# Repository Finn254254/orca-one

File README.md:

<div align="center">

# Orca One V1.0

### A custom Allwinner V3s single-board computer

Hardware design · PCB layout · ORCA OS testing · Bring-up documentation

</div>

> [!IMPORTANT]
> **Open-source hardware.** Orca One V1.0 is released under the CERN Open Hardware Licence Version 2 - Strongly Reciprocal (CERN-OHL-S-2.0). You may study, modify, manufacture, and redistribute the design subject to the license terms. See [LICENSE](LICENSE).

> [!WARNING]
> **Early hardware revision.** Orca One V1.0 has not been manufactured or tested yet. The board is currently waiting on funding before manufacturing.

## What is Orca One?

Orca One is the first test board for Orca servers. The main purpose of the board is to give us our own hardware to start testing ORCA OS on.

The first goal is simple: get our lightweight Linux-based ORCA OS to successfully boot on hardware we designed ourselves. This board is not meant to be a powerful Orca server yet. It is a starting point for testing the hardware and software before moving onto more complicated boards.

## Board renders

| Front | Back |
| :---: | :---: |
|  |  |

## Why I chose the Allwinner V3s

I chose the Allwinner V3s because it is a relatively easy and cheap chip to start with.

One of the biggest reasons was its package. The V3s uses an LQFP package instead of BGA, which makes the PCB easier to design and also makes the chip easier to solder.

It also has integrated RAM instead of requiring external DDR. This means I don't have to route a separate DDR chip for my first Linux board, while I can still get experience designing a board around a Linux-capable SoC.

## Main features

- Allwinner V3s SoC with integrated RAM
- 5 V USB-C power input
- 3.3 V, 3.0 V, 1.8 V, 1.2 V and 1.1 V power rails
- MicroSD storage and OS boot
- USB-A 2.0
- Ethernet
- GPIO expansion
- UART debugging
- Fan header
- Four-layer custom PCB

## Power system

The board is powered using 5 V over USB-C. The USB-C input is configured as a power sink using two 5.1 kΩ resistors on the CC pins.

From the 5 V input, the board generates the different voltages required by the V3s and the other parts of the board. These include 3.3 V, 3.0 V, 1.8 V, 1.2 V and 1.1 V.

I decided to design this power system instead of using a premade power module because I wanted to learn and get practice using power regulators and buck converters.

One of the main things I had to learn was how adjustable regulators use a feedback voltage divider. I had to use the regulator equations to work out the resistor values needed to generate the correct output voltages.

This was probably the hardest part of designing the schematic because it involved both understanding the circuit and doing the maths to make sure each rail had the correct voltage.

## Decoupling and bulk capacitors

Another part of the power design was adding the decoupling and bulk capacitors for the different rails.

This became one of the hardest parts when I moved onto the PCB layout. I needed to fit the capacitors close to the V3s power pins while still leaving enough room around the SoC to route everything else.

## MicroSD and ORCA OS

Orca One does not have any other onboard storage, so the MicroSD card is used to store and boot ORCA OS.

The first major software test for the physical board will be seeing if our OS can successfully boot from the MicroSD card.

## USB 2.0

Orca One has a USB-A 2.0 port for connecting USB devices to the board.

## Ethernet

Ethernet was added so Orca One can be managed remotely over the network using SSH.

This means that once ORCA OS is running, I should be able to connect to the board from another computer and manage it without needing a display or keyboard connected directly to Orca One.

## GPIO, UART and fan

The board also has headers for GPIO, UART and a fan.

UART gives me a way to debug the board, especially during the first boot attempts. The GPIO header exposes connections from the V3s for future testing and expansion, while the fan header gives the board a connection for cooling if needed.

## PCB layout

After completing the schematic, I moved onto designing the four-layer PCB.

One of the most difficult parts was placing the decoupling and bulk capacitors close to the SoC while also making sure there was enough room to route the rest of the board.

I also spent a lot of time working on the copper pours. The pours were changed many times during the PCB design as I worked out better ways to shape and position them around the board.

This ended up being one of the biggest things I learned from designing Orca One. Before this project I had much less experience using copper pours, but I now have a much better understanding of how to use and adjust them as part of a PCB layout.

## What I learned

Orca One has given me practice designing a complete board around a Linux-capable SoC instead of only working with individual smaller circuits.

Some of the main things I learned while making the board were:

- How to use and shape copper pours
- How to design multiple power rails
- How adjustable regulators and buck converters work
- How to calculate feedback voltage dividers
- How to place decoupling and bulk capacitors around an SoC
- How to design a board around a processor with multiple interfaces
- How the hardware and boot storage need to work together to boot an operating system

The biggest thing I learned during the PCB layout was how to use copper pours properly. I changed them several times while designing the board and gradually found better ways to fit them into the layout.

## Current status

Orca One V1.0 is currently waiting on funding before it can be manufactured.

Because the physical board does not exist yet, none of the hardware has been validated. The next major stage of the project is manufacturing and bring-up.

## First bring-up

Once the board has been manufactured and assembled, the first thing I want to find out is whether it powers on correctly.

After that, the main goal is to see if it can successfully boot ORCA OS from the MicroSD card.

Getting the board to power on and boot our own OS will be the first major test of Orca One and will let us start testing the hardware and software together.

## Design overview

The complete editable schematic is included in the KiCad project. Expand a section below for a quick visual tour.

<details>
<summary><strong>Power system</strong> — USB-C input and regulated power rails</summary>

### USB-C power input

### Regulated power rails

</details>

<details>
<summary><strong>External interfaces</strong> — USB-A, MicroSD, and Ethernet</summary>

### USB-A 2.0

### MicroSD card

### Ethernet

</details>

<details>
<summary><strong>Processor and supporting circuitry</strong> — Allwinner V3s and decoupling</summary>

### Decoupling and bulk capacitors

</details>

<details>
<summary><strong>Expansion and debug</strong> — fan, UART, and GPIO headers</summary>

</details>

## Repository contents

| Path | Contents |
| --- | --- |
| `hardware/kicad/` | KiCad 9 project, schematic, and four-layer PCB layout |
| `hardware/footprints/` | Custom Allwinner V3s LQFP-128 footprint |
| `bom/` | Bill of materials in CSV and XLSX formats |
| `manufacturing/` | Gerber/drill archive and component placement data |
| `images/` | Board photographs, schematic images and renders |

## Opening the design

1. Install KiCad 9 or a compatible newer release.
2. Open `hardware/kicad/ORCA First Linux Board.kicad_pro`.
3. The project-local footprint table maps the included `v3s` footprint library automatically.

The PCB currently references three optional component STEP models from the original designer's local computer, including the V3s processor and Ethernet connector models. They are not included, so KiCad may show those packages without 3D bodies until redistributable models are added.

## Manufacturing warning

Review the schematic, PCB, BOM, placement data, and fabrication outputs carefully before ordering or assembling boards.

This is the first hardware revision and has not yet been physically tested. Manufacturing outputs may also become stale as the editable design changes.

## License

Copyright © 2026 Finn Mather.

Orca One V1.0 is open-source hardware licensed under **CERN-OHL-S-2.0**. You may study, modify, manufacture, and redistribute the design under the terms of the license. See [LICENSE](LICENSE) for details.

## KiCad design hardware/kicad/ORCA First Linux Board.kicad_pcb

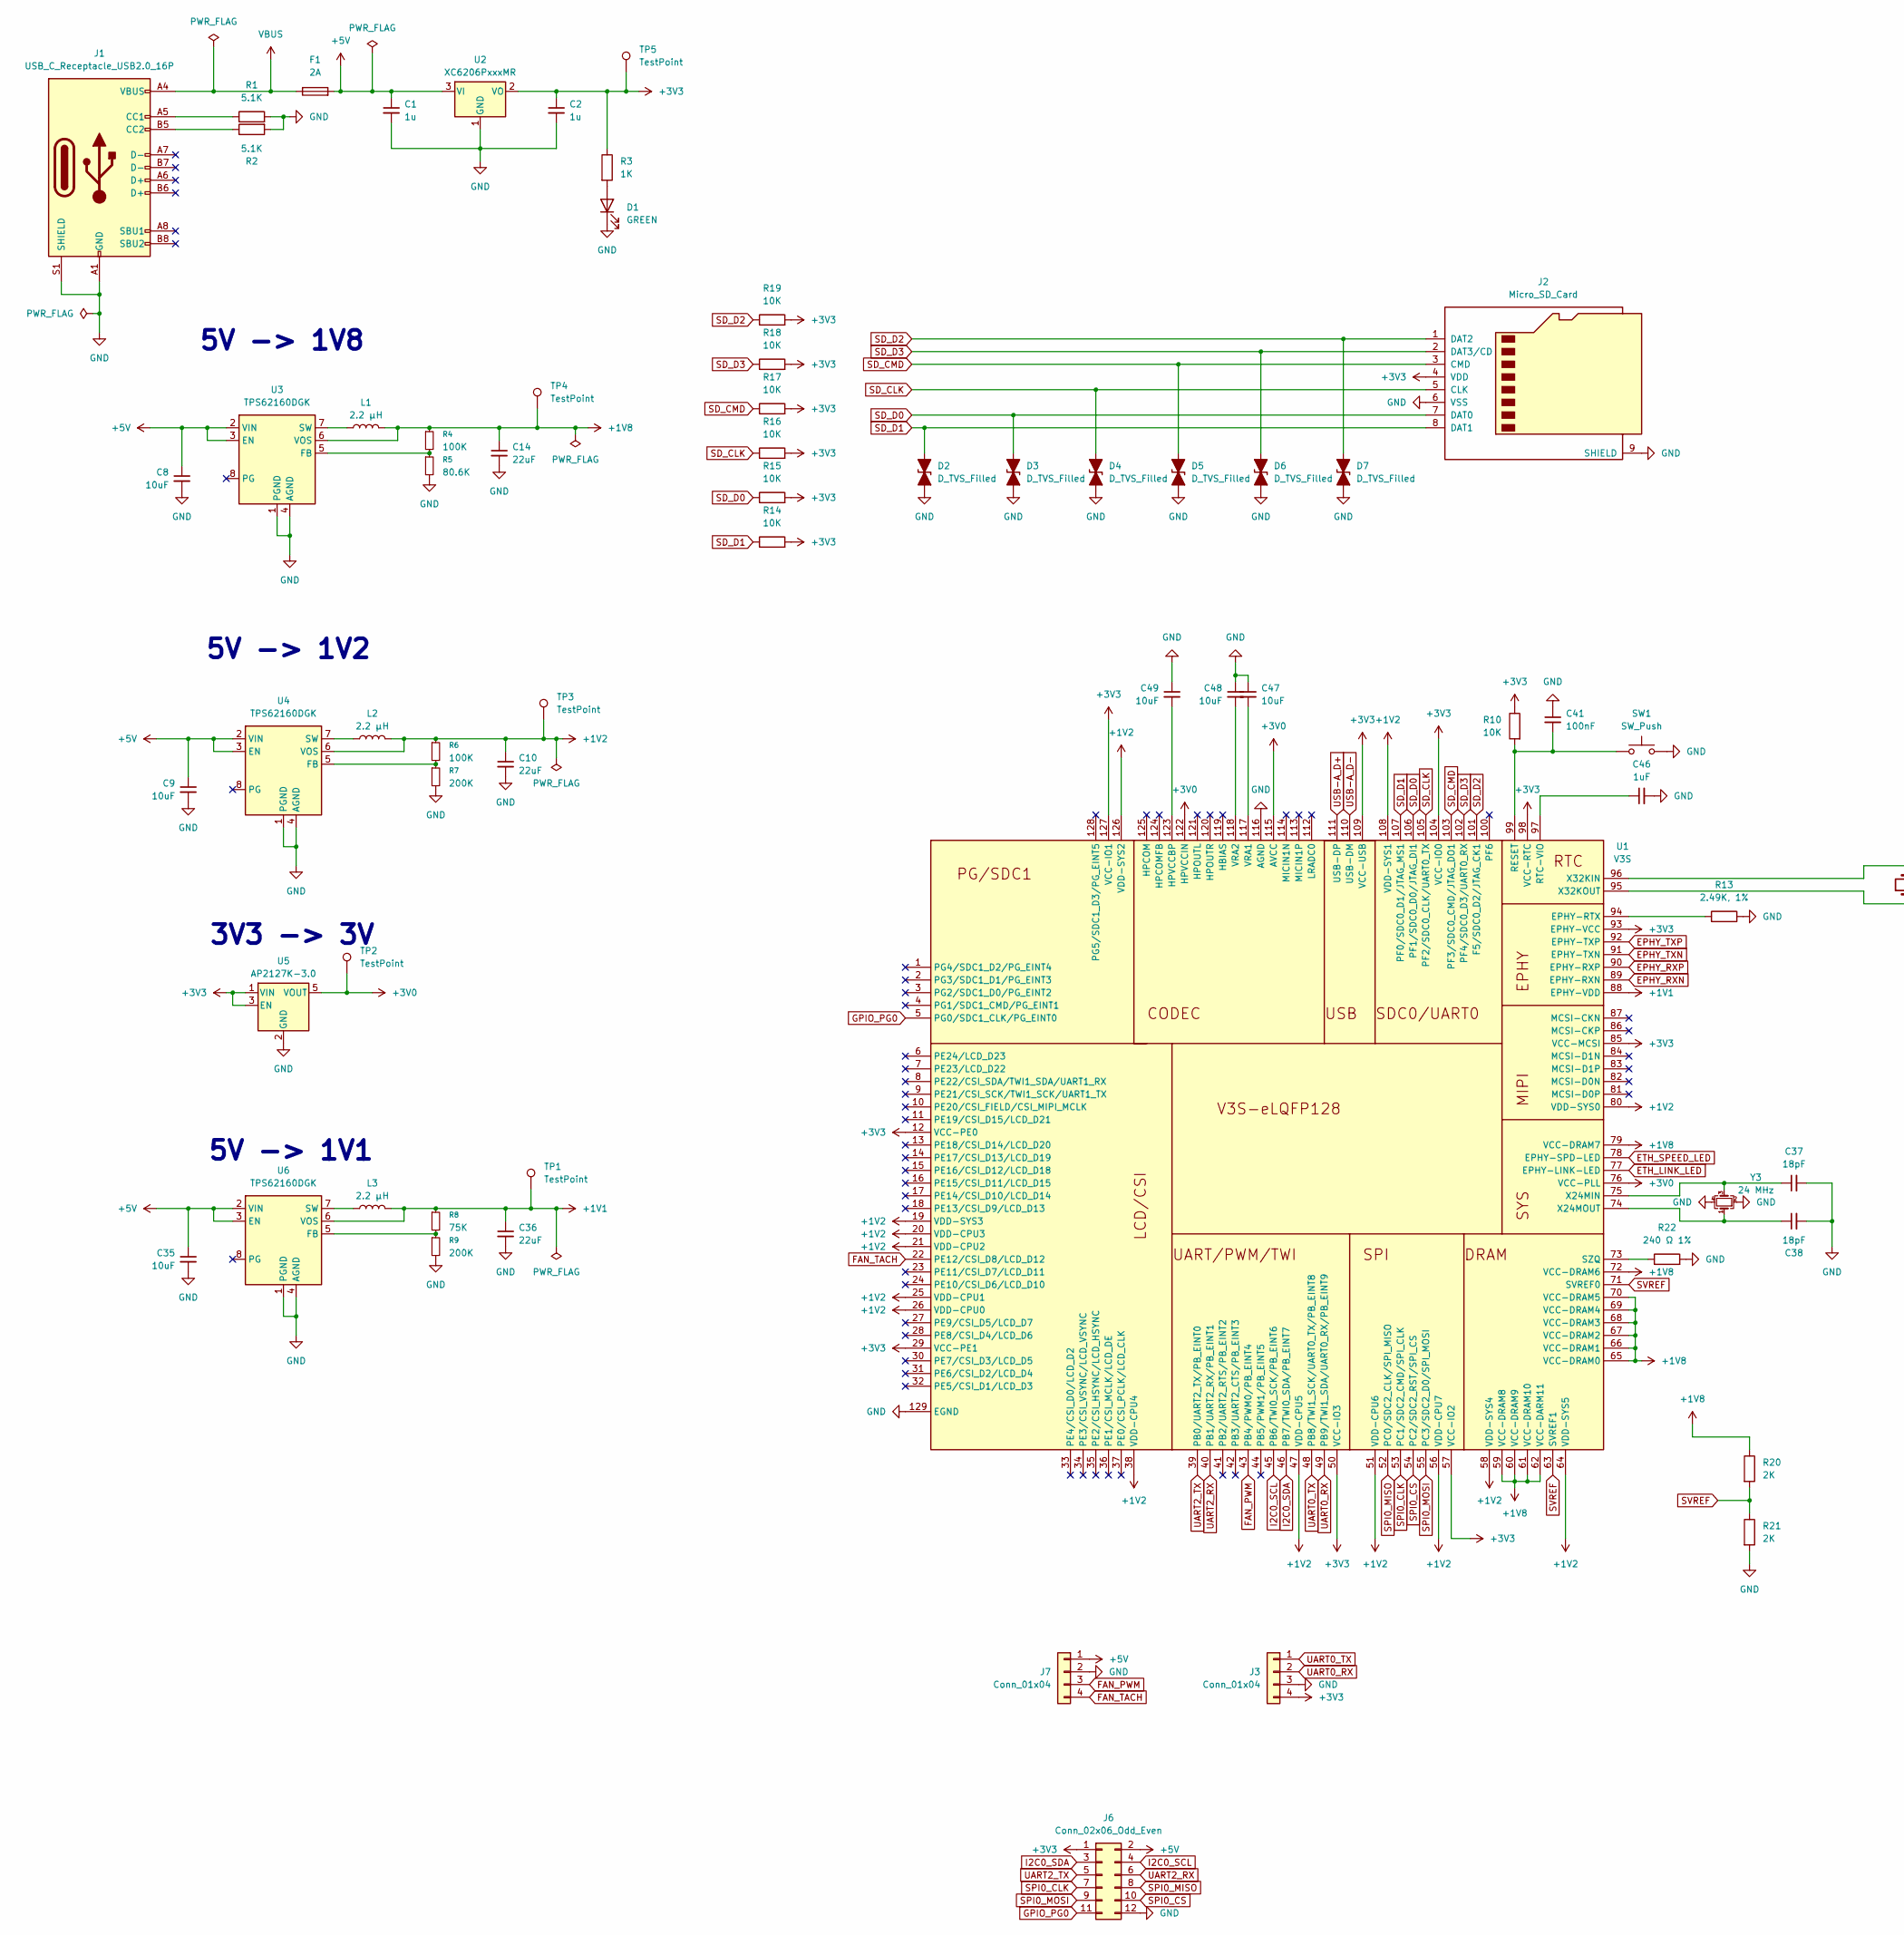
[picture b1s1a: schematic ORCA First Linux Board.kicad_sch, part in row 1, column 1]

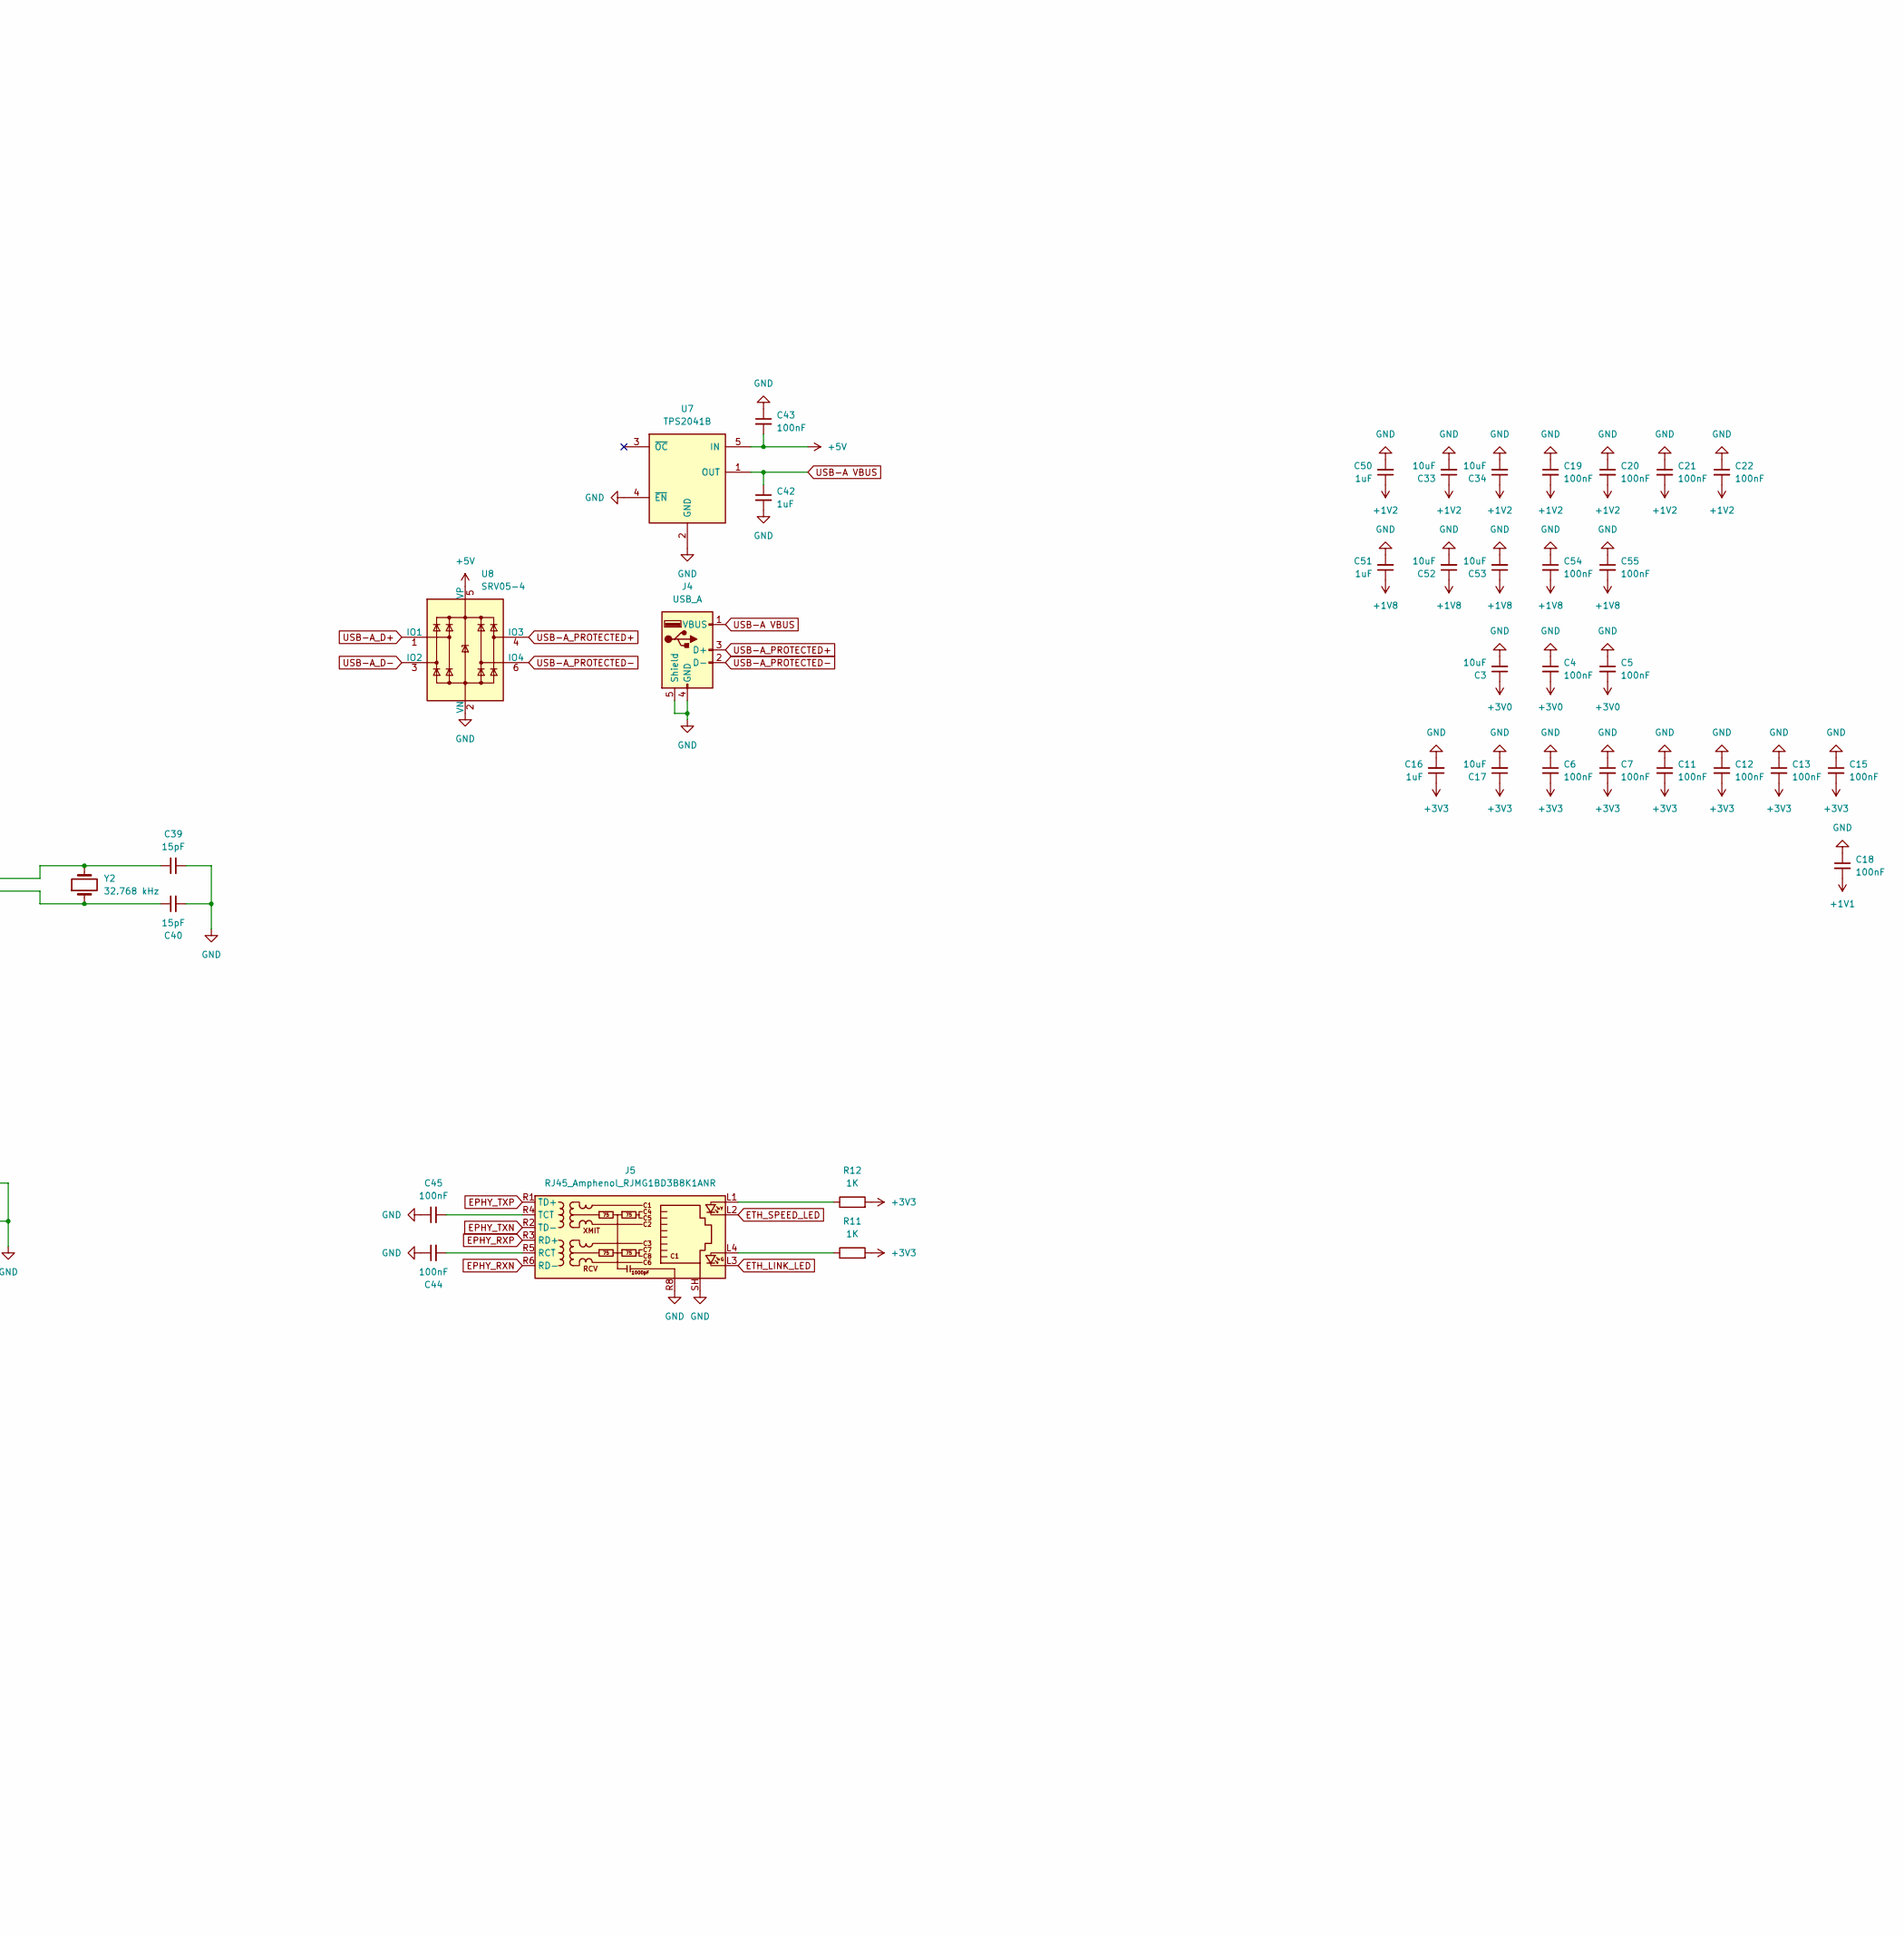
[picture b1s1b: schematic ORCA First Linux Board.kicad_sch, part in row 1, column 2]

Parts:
C1, C2: 1u; C_0603_1608Metric
C3, C8, C9, C17, C33, C34, C35, C47, C48, C49, C52, C53: 10uF; C_0805_2012Metric
C4, C5, C6, C7, C11, C12, C13, C15, C18, C19, C20, C21, C22, C41, C43, C44, C45, C54, C55: 100nF; C_0603_1608Metric
C10, C14, C36: 22uF; C_0805_2012Metric
C16, C50, C51: 1uF; C_0805_2012Metric
C37, C38: 18pF; C_0603_1608Metric
C39, C40: 15pF; C_0603_1608Metric
C42, C46: 1uF; C_0603_1608Metric
D1: GREEN; LED_0603_1608Metric
D2, D3, D4, D5, D6, D7: D_TVS_Filled; D_SOD-123F
F1: 2A; Fuse_1206_3216Metric
J1: USB_C_Receptacle_USB2.0_16P; USB_C_Receptacle_GCT_USB4105-xx-A_16P_TopMnt_Horizontal
J2: Micro_SD_Card; microSD_HC_Molex_104031-0811
J3, J7: Conn_01x04; PinHeader_1x04_P2.54mm_Vertical
J4: USB_A; USB_A_Molex_67643_Horizontal
J5: RJ45_Amphenol_RJMG1BD3B8K1ANR
J6: Conn_02x06_Odd_Even; PinSocket_2x06_P2.54mm_Vertical
L1, L2, L3: 2.2 µH; L_1210_3225Metric
R1, R2: 5.1K; R_0603_1608Metric
R3, R11, R12: 1K; R_0603_1608Metric
R4, R6: 100K; R_0603_1608Metric
R5: 80.6K; R_0603_1608Metric
R7, R9: 200K; R_0603_1608Metric
R8: 75K; R_0603_1608Metric
R10, R14, R15, R16, R17, R18, R19: 10K; R_0603_1608Metric
R13: 2.49K, 1%; R_0603_1608Metric
R20, R21: 2K; R_0603_1608Metric
R22: 240 Ω 1%; R_0603_1608Metric
SW1: SW_Push; SW_SPST_PTS645Sx43SMTR92
TP1, TP2, TP3, TP4, TP5: TestPoint; TestPoint_Pad_D1.5mm
U1: V3S; LQFP-128_L14.0-W14.0-P0.40-LS16.0-BL-EP5.0; Manufacturer Part V3s
U2: XC6206PxxxMR; SOT-23-3
U3, U4, U6: TPS62160DGK; MSOP-8_3x3mm_P0.65mm
U5: AP2127K-3.0; SOT-23-5
U7: TPS2041B; SOT-23-5
U8: SRV05-4; SOT-23-6
Y2: 32.768 kHz; Crystal_SMD_3215-2Pin_3.2x1.5mm
Y3: 24 MHz; Crystal_SMD_3225-4Pin_3.2x2.5mm

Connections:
+1V2: C10.1, C19.2, C20.2, C21.2, C22.2, C33.1, C34.1, C50.1, L2.2, R6.1, TP3.1, U1.19 (VDD-SYS3), U1.20 (VDD-CPU3), U1.21 (VDD-CPU2), U1.25 (VDD-CPU1), U1.26 (VDD-CPU0), U1.38 (VDD-CPU4), U1.47 (VDD-CPU5), U1.51 (VDD-CPU6), U1.56 (VDD-CPU7), U1.58 (VDD-SYS4), U1.64 (VDD-SYS5), U1.80 (VDD-SYS0), U1.108 (VDD-SYS1), U1.126 (VDD-SYS2), U4.6 (VOS)
+1V8: C14.1, C51.1, C52.1, C53.1, C54.2, C55.2, L1.2, R4.1, R20.1, TP4.1, U1.59 (VCC-DRAM8), U1.60 (VCC-DRAM9), U1.61 (VCC-DRAM10), U1.62 (VCC-DARM11), U1.65 (VCC-DRAM0), U1.66 (VCC-DRAM1), U1.67 (VCC-DRAM2), U1.68 (VCC-DRAM3), U1.69 (VCC-DRAM4), U1.70 (VCC-DRAM5), U1.72 (VCC-DRAM6), U1.79 (VCC-DRAM7), U3.6 (VOS)
+3V0: C3.1, C4.2, C5.2, TP2.1, U1.76 (VCC-PLL), U1.115 (AVCC), U1.122 (HPVCCIN), U5.5 (VOUT)
+3V3: C2.1, C6.2, C7.2, C11.2, C12.2, C13.2, C15.2, C16.1, C17.1, J2.4 (VDD), J3.4, J6.1, R3.1, R10.1, R11.2, R12.2, R14.2, R15.2, R16.2, R17.2, R18.2, R19.2, TP5.1, U1.12 (VCC-PE0), U1.29 (VCC-PE1), U1.50 (VCC-IO3), U1.57 (VCC-IO2), U1.85 (VCC-MCSI), U1.93 (EPHY-VCC), U1.98 (VCC-RTC), U1.104 (VCC-IO0), U1.109 (VCC-USB), U1.127 (VCC-IO1), U2.2 (VO), U5.1 (VIN), U5.3 (EN)
+5V: C1.1, C8.1, C9.1, C35.1, C43.2, F1.2, J6.2, J7.1, U2.3 (VI), U3.2 (VIN), U3.3 (EN), U4.2 (VIN), U4.3 (EN), U6.2 (VIN), U6.3 (EN), U7.5 (IN), U8.5 (VP)
EPHY_RXN: J5.R6 (RD-), U1.89 (EPHY-RXN)
EPHY_RXP: J5.R3 (RD+), U1.90 (EPHY-RXP)
EPHY_TXN: J5.R2 (TD-), U1.91 (EPHY-TXN)
EPHY_TXP: J5.R1 (TD+), U1.92 (EPHY-TXP)
ETH_LINK_LED: J5.L3, U1.77 (EPHY-LINK-LED)
ETH_SPEED_LED: J5.L2, U1.78 (EPHY-SPD-LED)
FAN_PWM: J7.3, U1.43 (PB4/PWM0/PB_EINT4)
FAN_TACH: J7.4, U1.22 (PE12/CSI_D8/LCD_D12)
GPIO_PG0: J6.11, U1.5 (PG0/SDC1_CLK/PG_EINT0)
I2C0_SCL: J6.4, U1.45 (PB6/TWI0_SCK/PB_EINT6)
I2C0_SDA: J6.3, U1.46 (PB7/TWI0_SDA/PB_EINT7)
unnamed: D1.2 (A), R3.2
unnamed: J1.A5 (CC1), R1.1
unnamed: J1.B5 (CC2), R2.1
unnamed: J5.L1, R12.1
unnamed: J5.L4, R11.1
unnamed: C44.2, J5.R5 (RCT)
unnamed: C45.2, J5.R4 (TCT)
unnamed: R13.2, U1.94 (EPHY-RTX)
unnamed: C49.2, U1.123 (HPVCCBP)
unnamed: C41.2, R10.2, SW1.1, U1.99 (RESET)
unnamed: C46.1, U1.97 (RTC-VIO)
unnamed: R22.1, U1.73 (SZQ)
unnamed: C47.2, U1.117 (VRA1)
unnamed: C48.2, U1.118 (VRA2)
unnamed: C37.1, U1.75 (X24MIN), Y3.3
unnamed: C38.1, U1.74 (X24MOUT), Y3.1
unnamed: C39.1, U1.96 (X32KIN), Y2.2
unnamed: C40.1, U1.95 (X32KOUT), Y2.1
unnamed: R4.2, R5.1, U3.5 (FB)
unnamed: L1.1, U3.7 (SW)
unnamed: R6.2, R7.1, U4.5 (FB)
unnamed: L2.1, U4.7 (SW)
unnamed: R8.2, R9.1, U6.5 (FB)
unnamed: L3.1, U6.7 (SW)
SD_CLK: D4.2 (A2), J2.5 (CLK), R16.1, U1.105 (PF2/SDC0_CLK/UART0_TX)
SD_CMD: D5.2 (A2), J2.3 (CMD), R17.1, U1.103 (PF3/SDC0_CMD/JTAG_DO1)
SD_D0: D3.2 (A2), J2.7 (DAT0), R15.1, U1.106 (PF1/SDC0_D0/JTAG_DI1)
SD_D1: D2.2 (A2), J2.8 (DAT1), R14.1, U1.107 (PF0/SDC0_D1/JTAG_MS1)
SD_D2: D7.2 (A2), J2.1 (DAT2), R19.1, U1.101 (F5/SDC0_D2/JTAG_CK1)
SD_D3: D6.2 (A2), J2.2 (DAT3/CD), R18.1, U1.102 (PF4/SDC0_D3/UART0_RX)
SPI0_CLK: J6.7, U1.53 (PC1/SDC2_CMD/SPI_CLK)
SPI0_CS: J6.10, U1.54 (PC2/SDC2_RST/SPI_CS)
SPI0_MISO: J6.8, U1.52 (PC0/SDC2_CLK/SPI_MISO)
SPI0_MOSI: J6.9, U1.55 (PC3/SDC2_D0/SPI_MOSI)
SVREF: R20.2, R21.1, U1.63 (SVREF1), U1.71 (SVREF0)
UART0_RX: J3.2, U1.49 (PB9/TWI1_SDA/UART0_RX/PB_EINT9)
UART0_TX: J3.1, U1.48 (PB8/TWI1_SCK/UART0_TX/PB_EINT8)
UART2_RX: J6.6, U1.40 (PB1/UART2_RX/PB_EINT1)
UART2_TX: J6.5, U1.39 (PB0/UART2_TX/PB_EINT0)
USB-A VBUS: C42.1, J4.1 (VBUS), U7.1 (OUT)
USB-A_D+: U1.111 (USB-DP), U8.1 (IO1)
USB-A_D-: U1.110 (USB-DM), U8.3 (IO2)
USB-A_PROTECTED+: J4.3 (D+), U8.4 (IO3)
USB-A_PROTECTED-: J4.2 (D-), U8.6 (IO4)
VBUS: F1.1, J1.A4 (VBUS), J1.A9 (VBUS), J1.B4 (VBUS), J1.B9 (VBUS)

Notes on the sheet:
3V3 -> 3V
5V -> 1V2
5V -> 1V8
5V -> 1V1

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
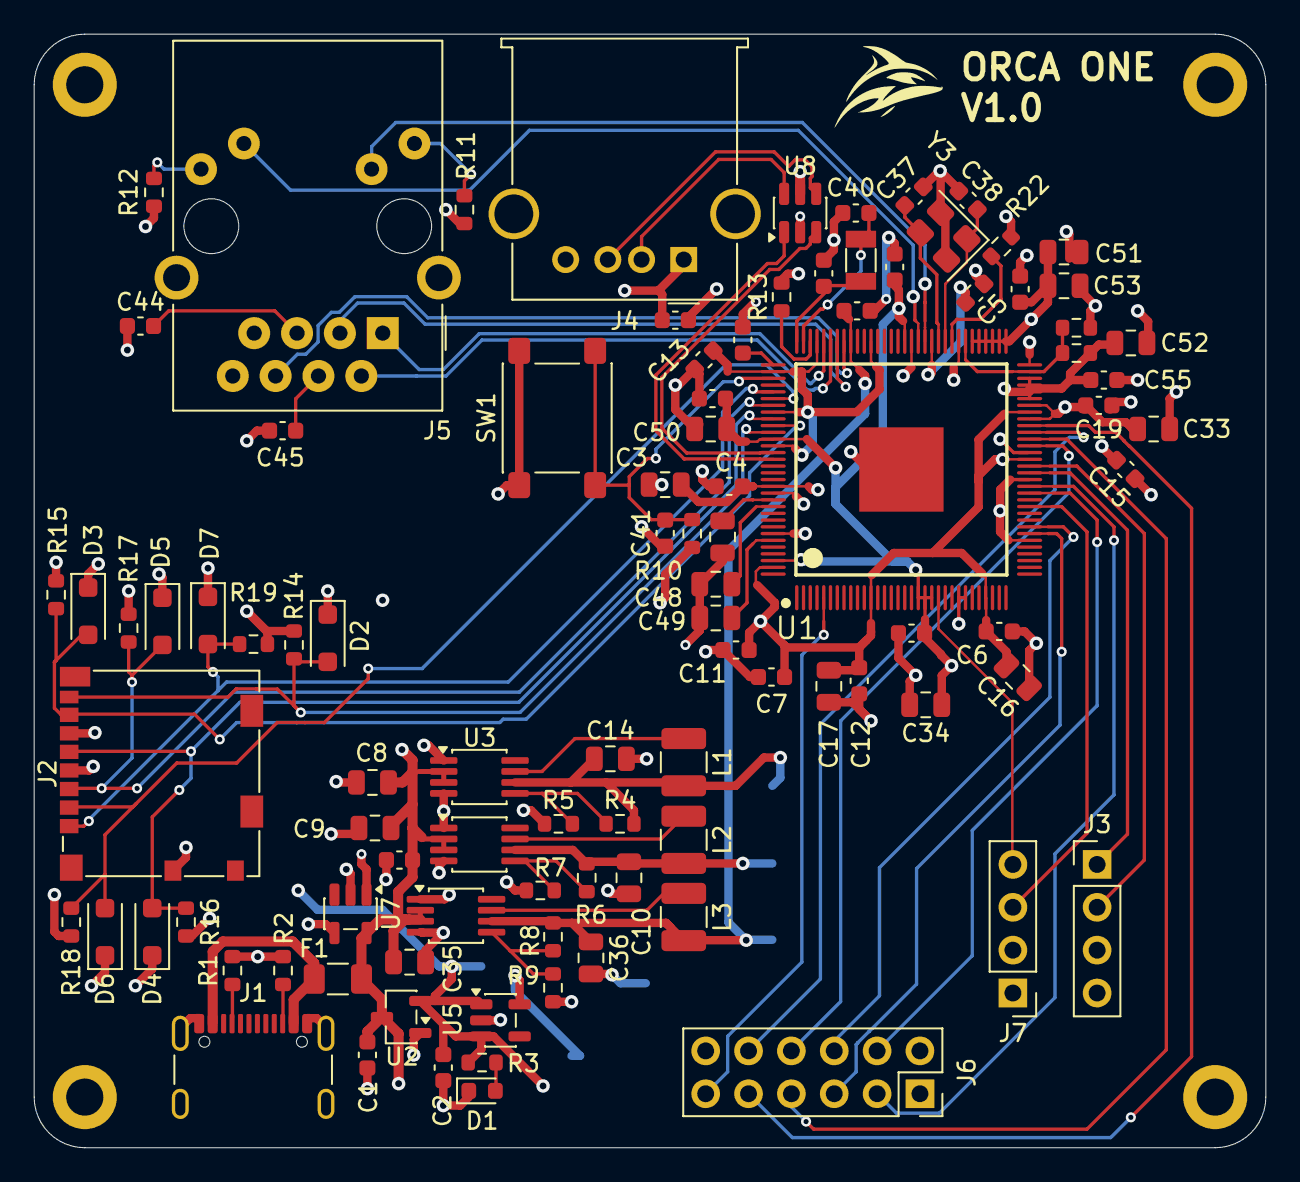
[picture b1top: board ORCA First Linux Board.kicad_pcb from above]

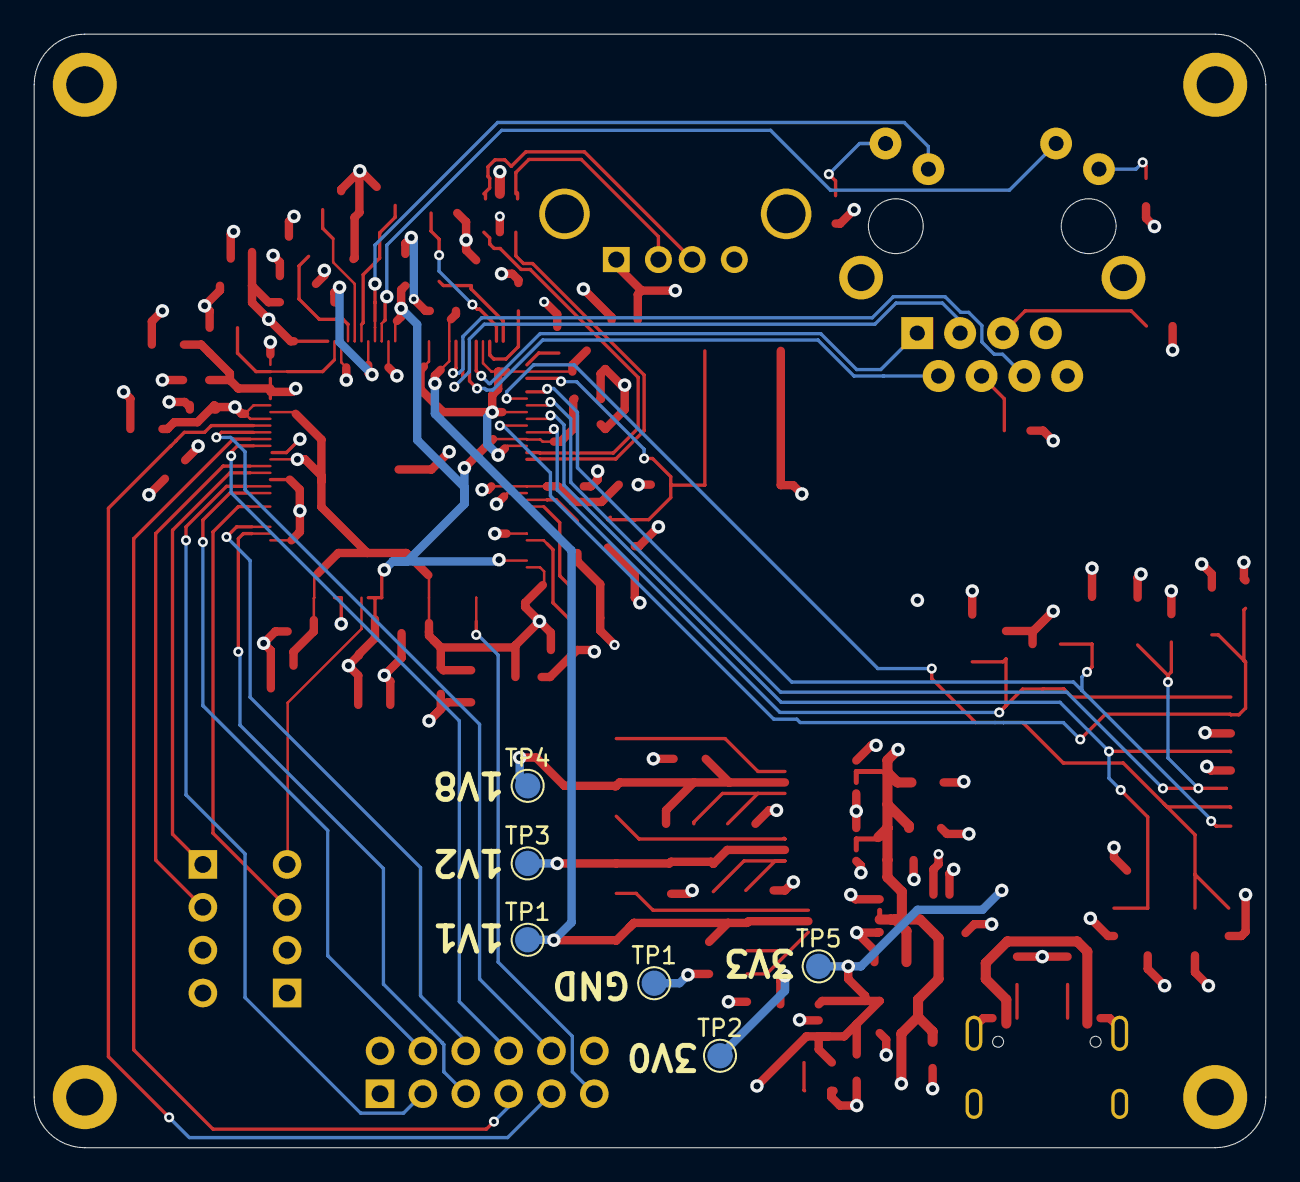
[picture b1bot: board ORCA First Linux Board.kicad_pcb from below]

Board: 4 copper layers, 73.0 x 66.0 mm, 102 parts (6 on the bottom side), 63 nets.

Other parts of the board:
TP1#2: TestPoint; TestPoint_Pad_D1.5mm
